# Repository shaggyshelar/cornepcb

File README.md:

# samoklava

## An autogenerated split 36 key keyboard

## Disclaimer

This is an early experimental prototype. Please do not rely on the autogenerated files and double check them manually
before sending them off to a PCB fab. The author and other random strangers on the internet have been able to produce
working keyboard prototypes from this repo; this does not mean that everything will work every time.

The author(s) waive(s) responsibility for any damage or regulatory violations caused by using this software (see
license). Please consult your local regulations around radio frequencies and what's allowed for DIY projects in your
country.

| left                            | right                           |
| ------------------------------- | ------------------------------- |
|  |  |

A 5x3 split keyboard with 3 thumb keys. There is nothing unique about the keyboard layout. It's inspired by Corne and
Kyria, and has the exact number of keys needed for the [Miryoku](https://github.com/manna-harbour/miryoku) layout.

The interesting thing about this keyboard is that it's a declarative design:

- Layout is declared using [Ergogen](https://github.com/mrzealot/ergogen/). See [this fork](https://github.com/soundmonster/ergogen).
- The build system uses Ergogen to translate YAML to a KiCad PCB and plate files for FR-4 fab or laser cutting
- uses [kicad-automation-scripts](https://github.com/productize/kicad-automation-scripts) and [FreeRouting](https://github.com/freerouting/freerouting) to **automatically route the traces on the PCB**
- uses [KiKit](https://github.com/yaqwsx/KiKit) to render PCB previews (see top of this file) and production-ready **Gerber files**

## Features

- Extra pins and a slider switch for battery for wireless Promicro clones (tested with nice!nano); the slider can be
  shorted with a jumper if `CONFIG_ZMK_SLEEP` is preferred.
- Wired operation with QMK should be possible but is not tested; TRRS footprints are included and routed. The pinout is
  identical with a five-column Corne sans the RGBLEDs.
- Reset switches are easily accessible. The footprints used are the same as on the Corne.

## How to

If you would like to modify this:

- fork it
- change `samoklava.yaml` to your liking
- push your changes; the `build.yml` GitHub Workflow will pick it up, autoroute and generate Gerbers, all in a zip file.
  See https://github.com/soundmonster/samoklava/actions
- or:
  - make sure to have Docker CLI and NodeJS installed
  - run `make setup clean all`
  - check the `output` folder for KiCad PCBs and Gerbers

See the [workflow](.github/workflows/build.yml) or the [Makefile](Makefile) for more details.
See [my ZMK config](https://github.com/soundmonster/samoklava-zmk-config) for a suggested keymap.

# Initialize

`make run init-footprint`

## Update following file and add below code

/node_modules/ergogen/src/footprints/index.js

`   bat: require('./bat'),
    b3u1000p: require('./b3u1000p'),
    pcm12: require('./pcm12'),
    promicro_pretty: require('./promicro_pretty')`

## Once files are generated then run following plugins

- freerouting
- Teardrops
- Round Tracks

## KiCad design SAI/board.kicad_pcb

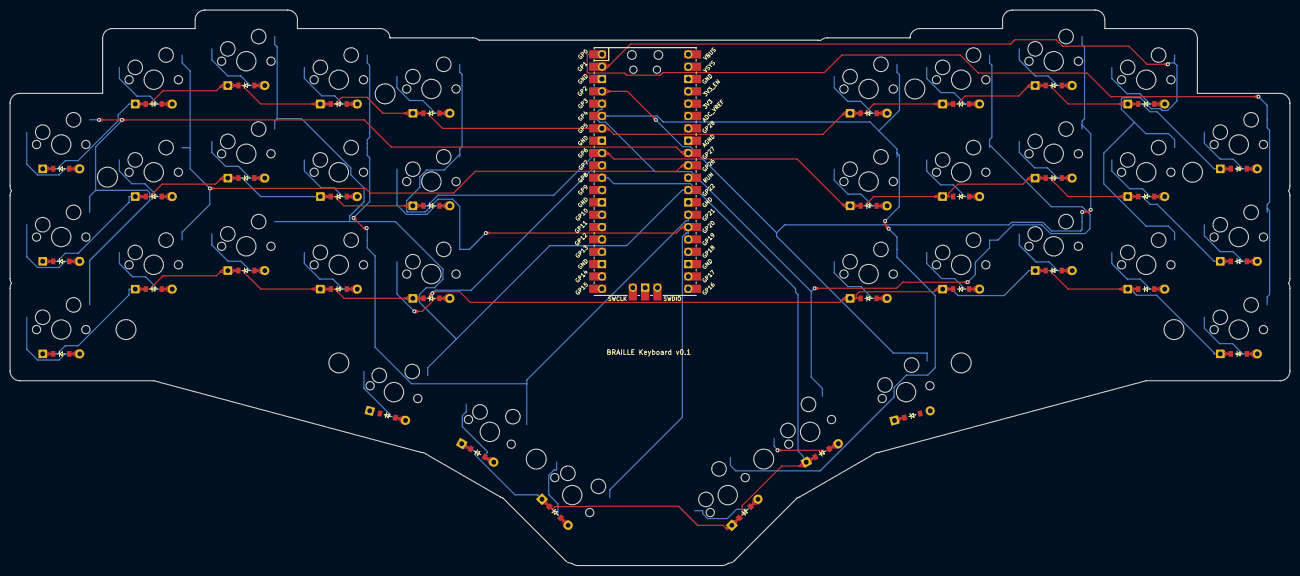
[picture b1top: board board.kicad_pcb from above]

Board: 2 copper layers, 263.5 x 114.3 mm, 73 parts (0 on the bottom side), 50 nets.

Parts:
D1, D2, D3, D4, D5, D6, D7, D8, D9, D10, D11, D12, D13, D14, D15, D16, D17, D18, D19, D20, D21, D22, D23, D24, D25, D26, D27, D28, D29, D30, D31, D32, D33, D34, D35, D36: ComboDiode
MCU1: RPi_Pico_SMD_TH
S1, S2, S3, S4, S5, S6, S7, S8, S9, S10, S11, S12, S13, S14, S15, S16, S17, S18, S19, S20, S21, S22, S23, S24, S25, S26, S27, S28, S29, S30, S31, S32, S33, S34, S35, S36: MX

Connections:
C1: MCU1.32, S1.2, S2.2, S3.2
C2: MCU1.31, S4.2, S5.2, S6.2
C3: MCU1.29, S7.2, S8.2, S9.2, S16.2
C4: MCU1.27, S10.2, S11.2, S12.2, S17.2
C5: MCU1.26, S13.2, S14.2, S15.2, S18.2
C6: MCU1.6, S31.2, S32.2, S33.2, S36.2
C7: MCU1.5, S28.2, S29.2, S30.2, S35.2
C8: MCU1.4, S25.2, S26.2, S27.2, S34.2
C9: MCU1.2, S22.2, S23.2, S24.2
C10: MCU1.1, S19.2, S20.2, S21.2
R1: D3.1, D3.2, D6.1, D6.2, D9.1, D9.2, D12.1, D12.2, D15.1, D15.2, D21.1, D21.2, D24.1, D24.2, D27.1, D27.2, D30.1, D30.2, D33.1, D33.2, MCU1.7
R2: D2.1, D2.2, D5.1, D5.2, D8.1, D8.2, D11.1, D11.2, D14.1, D14.2, D20.1, D20.2, D23.1, D23.2, D26.1, D26.2, D29.1, D29.2, D32.1, D32.2, MCU1.9
R3: D1.1, D1.2, D4.1, D4.2, D7.1, D7.2, D10.1, D10.2, D13.1, D13.2, D19.1, D19.2, D22.1, D22.2, D25.1, D25.2, D28.1, D28.2, D31.1, D31.2, MCU1.10
R4: D16.1, D16.2, D17.1, D17.2, D18.1, D18.2, D34.1, D34.2, D35.1, D35.2, D36.1, D36.2, MCU1.11
far_thumb: D18.1, D18.2, S18.1
home_thumb: D17.1, D17.2, S17.1
index_bottom: D10.1, D10.2, S10.1
index_home: D11.1, D11.2, S11.1
index_top: D12.1, D12.2, S12.1
inner_bottom: D13.1, D13.2, S13.1
inner_home: D14.1, D14.2, S14.1
inner_top: D15.1, D15.2, S15.1
middle_bottom: D7.1, D7.2, S7.1
middle_home: D8.1, D8.2, S8.1
middle_top: D9.1, D9.2, S9.1
mirror_far_thumb: D36.1, D36.2, S36.1
mirror_home_thumb: D35.1, D35.2, S35.1
mirror_index_bottom: D28.1, D28.2, S28.1
mirror_index_home: D29.1, D29.2, S29.1
mirror_index_top: D30.1, D30.2, S30.1
mirror_inner_bottom: D31.1, D31.2, S31.1
mirror_inner_home: D32.1, D32.2, S32.1
mirror_inner_top: D33.1, D33.2, S33.1
mirror_middle_bottom: D25.1, D25.2, S25.1
mirror_middle_home: D26.1, D26.2, S26.1
mirror_middle_top: D27.1, D27.2, S27.1
mirror_near_thumb: D34.1, D34.2, S34.1
mirror_pinky_bottom: D19.1, D19.2, S19.1
mirror_pinky_home: D20.1, D20.2, S20.1
mirror_pinky_top: D21.1, D21.2, S21.1
mirror_ring_bottom: D22.1, D22.2, S22.1
mirror_ring_home: D23.1, D23.2, S23.1
mirror_ring_top: D24.1, D24.2, S24.1
near_thumb: D16.1, D16.2, S16.1
pinky_bottom: D1.1, D1.2, S1.1
pinky_home: D2.1, D2.2, S2.1
pinky_top: D3.1, D3.2, S3.1
ring_bottom: D4.1, D4.2, S4.1
ring_home: D5.1, D5.2, S5.1
ring_top: D6.1, D6.2, S6.1

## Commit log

2022-12-16 Added copy script when boards are generated
2022-12-16 Code cleanup
2022-12-16 Add footprint config for b3u100p component
2022-12-16 Add footprint config for bat, pcm12, promicro_pretty component
2022-12-17 Updated simple vai in SAI.kicad_pcb for initial PCB with only via
2022-12-17 Added only PiPico footprint
2022-12-17 Initial config of pi-pico footprint
2022-12-17 Updated sai.yaml to include pi_pico
2022-12-17 Added missing footprint config for pi_pico
2022-12-17 Completed pi pico footprint config
2022-12-17 Absolum basic configs
2022-12-17 Updated matrix pinout numbers
2022-12-17 Added mapping for R1 net
2022-12-17 Completed mapping of C1 to C10 and R1 to R4
2022-12-17 Minor updates
2022-12-20 Added right side configuration
2022-12-20 Added all side
2022-12-20 Added glue example
2022-12-21 Added glue config
2022-12-21 Update main file
2022-12-21 Working backup of left side
2022-12-21 Working with both configs
2022-12-21 Added bind values
2022-12-21 Added pico area
2022-12-21 Added mirror column nets
2022-12-21 Updated keycap spacing
2022-12-21 Added mirror screw holes
2022-12-21 Updated mounting holes
2022-12-21 Updated build config to include init process
2022-12-21 Added updateIndex.js file to display content of footprint/index.js
2022-12-21 Added script updateIndex.js
2022-12-21 Updated displayContent
2022-12-21 Write mode file
2022-12-22 Updated PI Pico schematics and footprint to map unconnected pins
2022-12-22 Added edge cuts to Pico and now no warning or errors in DRC
2022-12-22 Added separate files for Pico kicad configs
2022-12-22 Fixed screw holes issue
2022-12-24 Working PCB with 6 DRC warnings
2022-12-24 Added I2C scan, ssd1306 sample
2022-12-24 I2C square bitmap example
2022-12-24 Simple static four menu display
2022-12-25 Added ESP32-S3-Devkit footprint
2022-12-25 Initial config of esp32s3_devkit
2022-12-25 Added row and column config for esp32
2022-12-25 Updated touchpad configs
2022-12-25 Added square pcb area
2022-12-25 Updated text positions
2022-12-25 Added OLED configs
2022-12-25 Added i2c
2022-12-29 Partial changes related to max98357
